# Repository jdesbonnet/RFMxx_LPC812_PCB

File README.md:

# RFM69HW and RFM98W experimentation board with option for LPC812/LPC824 MCU

This is a PCB board to experiment with HopeRF RFM69HW and RFM98 radio modules (or any modules in that family with a compatible footprint). 

The module can be accessed directly throught JP1 which breaks out the modules SPI bus and a few other pins.

Alternatively a LPC812 (ARM Cortex-M0+ MCU) can be soldered on the board as a controller. Firmware for the LPC812 is here: https://github.com/jdesbonnet/RFM69_LPC812_firmware

There is a blog post discussing this in more detail here: 
http://jdesbonnet.blogspot.ie/2014/12/experiments-with-rfm69-433mhz-digital.html

# Pinout

## Common to RFM69 and RFM98 boards

Leftmost column of 6 pins (from top to bottom): RESET, UART_TXD, UART_RXD, NC, ISP_ENTRY, GND.

Second column from left of 3 pins (from top to bottom): SWD_CLOCK, SWD_DATA, NC.

## RFM69
Three pin row above MCU (from left to right): 3.3V, GND, NC.

## RFM98 
Three pin row at top-right corner of the board (from left to right):  3.3V, GND, NC.

NC: not connect. SWD: serial wire debug. 

# Lessons from first iteration of PCB
 * Keep spacing of headers and test pads snapped to 0.1in grid to facilitate easy construction of bed of nails test rig on proto board.
 * Include power and ground on all headers even if it duplicates.
 * For traces that may become optional use 0 ohm jumper resistors to complete link, or use test pads to allow easy reconnection if a trace needs to be cut (undoing a manually cut trace is a pain).
 * Choice of font on v1 board was too small.
 * Consider side SMA connector
 
 # Version 2 PCB using LPC824

[Version 2 project files](./RFM98LPC824)

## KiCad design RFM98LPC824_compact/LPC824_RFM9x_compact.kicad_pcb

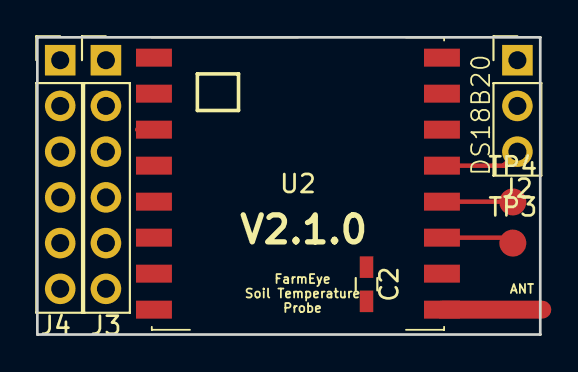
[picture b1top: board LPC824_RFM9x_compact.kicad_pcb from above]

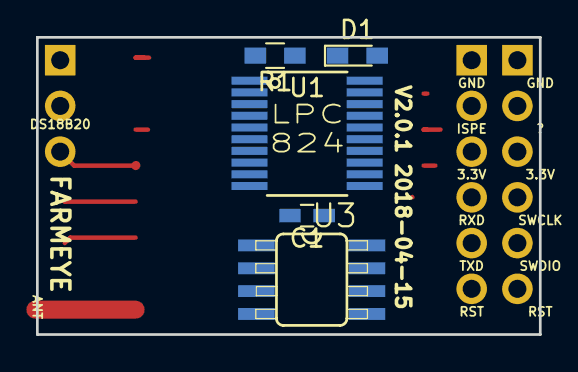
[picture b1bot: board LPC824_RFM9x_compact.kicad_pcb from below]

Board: 2 copper layers, 27.9 x 16.5 mm, 12 parts (5 on the bottom side), 21 nets.

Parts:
C1, C2: C; C_0603_HandSoldering
D1: LED; LED_0603_HandSoldering
J2: Conn_01x03; Pin_Header_Straight_1x03_Pitch2.54mm
J3, J4: Conn_01x06; Pin_Header_Straight_1x06_Pitch2.54mm
R1: R; R_0603_HandSoldering
TP3, TP4: TEST; Measurement_Point_Round-SMD-Pad_Small
U1: LPC824M201JDH20; TSSOP-20_4.4x6.5mm_Pitch0.65mm
U2: RFM92/95/96/97/98; Hopref_RFM9XW_SMD
U3: AT25_EEPROM; SO08

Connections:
3.3V: C1.1, C2.1, J2.3, J3.3, J4.3, U1.15, U1.18, U2.13, U3.8
DIO0: U1.1, U2.14
DIO3: TP3.1, U2.11
DIO4: TP4.1, U2.12
DS18B20: J2.2, U1.10
FLASH_CS: U1.9, U3.1
GND: C1.2, C2.2, J2.1, J3.1, J4.1, R1.1, U1.16, U1.17, U2.1, U2.8, U2.10, U3.4
GPIO13: J4.2, U1.3
ISPE: J3.2, U1.4
LED: D1.2, U1.2
MISO: U1.14, U2.2, U3.2
MOSI: U1.13, U2.3, U3.5
unnamed: D1.1, R1.2
RESET: J3.6, J4.6, U1.5
RFM_CS: U1.20, U2.5
RFM_RST: U1.11, U2.6
RXD: J3.4, U1.19
SCK: U1.12, U2.4, U3.6
SWCLK: J4.4, U1.7
SWDIO: J4.5, U1.8
TXD: J3.5, U1.6

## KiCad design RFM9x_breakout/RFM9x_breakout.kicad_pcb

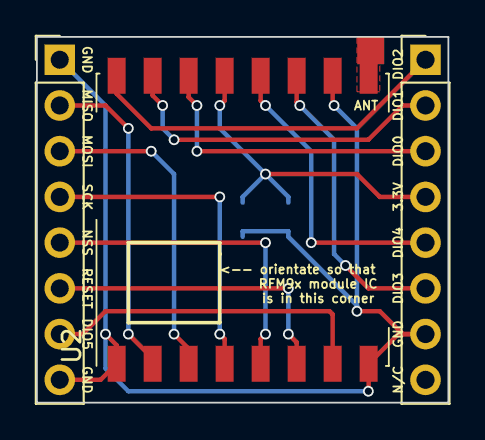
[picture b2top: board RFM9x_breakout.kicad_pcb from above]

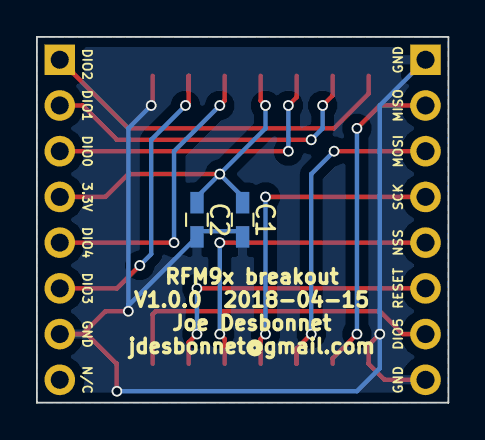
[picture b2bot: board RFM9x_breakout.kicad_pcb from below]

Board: 2 copper layers, 22.9 x 20.3 mm, 5 parts (2 on the bottom side), 13 nets.

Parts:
C1, C2: C; C_0603_HandSoldering
J1, J2: Conn_01x08_Male; Pin_Header_Straight_1x08_Pitch2.54mm
U2: RFM92/95/96/97/98; Hopref_RFM9XW_SMD

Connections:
3.3V: C1.1, C2.1, J2.4, U2.13
GND: C1.2, C2.2, J1.1, J1.8, J2.7, U2.1, U2.8, U2.10
unnamed: J1.2, U2.2
unnamed: J1.3, U2.3
unnamed: J1.4, U2.4
unnamed: J1.5, U2.5
unnamed: J1.6, U2.6
unnamed: J1.7, U2.7
unnamed: J2.1, U2.16
unnamed: J2.2, U2.15
unnamed: J2.3, U2.14
unnamed: J2.5, U2.12
unnamed: J2.6, U2.11

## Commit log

2014-11-03 RFM98W done
2014-11-03 Add RFM69HW device
2014-11-04 move some pins around on RFM69
2014-11-04 first commit of RFMxx board
2014-11-04 no comment
2014-11-05 reasonably good layout on RFM98 side
2014-11-05 start working on RFM69
2014-11-05 start removing ground plane on RFM98 side
2014-11-06 LEDs on DIO0
2014-11-06 trace bug fixes
2014-11-06 attempting to separate vcc, gnd on both sides of the board
2014-11-06 getting close to done
2014-11-07 fixed inconsistency by hand editing .brd XML
2014-11-07 added TPs for DIO0..5 on RFM69 side
2014-11-07 better routing of power to RFM98
2014-11-07 some refinements
2014-11-07 some tidyup before Rev 1
2014-11-07 Remove markings from bottom of board. Failed to reduce quote, so must be the TPs.
2014-11-08 Removed TPs, now quote back down to the EUR 85 level.
2014-11-08 fix some clearance issues which is pushing up the price due to using thinner copper foil
2014-11-08 increase dia of vias: this finally brings the Eurocircuits quote back down to the same level as an earlier version of the board.
2014-11-08 cosmetic changes to board lables
2014-11-08 label cosmetic changes
2014-11-08 more cosmetic changes
2014-11-08 extra holes on dividing line
2014-11-16 Via between RXD on UART connector to PIO0_0 was too close to 3.3V line and merged in V1 of PCB. Move via.
2016-04-24 photo of populated RFM69HW board
2016-08-14 add PCB layout image
2016-08-14 add pinout info
2016-08-14 add image of schematic
2018-04-14 v2.0.0 schematic and layout
2018-04-14 lib files
2018-04-14 move SPI flash MISO trace away from MOSI
2018-04-15 gerber file sent to OSHPark
2018-04-15 add README.md
2018-04-15 add missing RFM_CS trace
2018-04-15 add GPIO11 test pad
2018-04-15 RFM9x breakout
2018-04-15 move RFM9x_breakout to separate github repo
2018-04-15 hand solder friendly pads (extended length)
2018-04-15 LPC824/RFM9x board v2.0.1
2018-04-19 RFM9x compact board
2018-05-13 add 3D rendering
2018-10-16 Add J3, J4 programming header pinout
2018-11-11 kicad 6.0
2018-11-11 schematic
